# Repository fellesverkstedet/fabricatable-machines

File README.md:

# Full documention on the [wiki page](https://github.com/fellesverkstedet/fabricatable-machines/wiki)

License: [Creative commons Attribution-ShareAlike 4.0](https://creativecommons.org/licenses/by-sa/4.0/)

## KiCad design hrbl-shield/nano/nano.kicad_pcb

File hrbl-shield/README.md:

# Hrbl - Grbl shield for integrated motors

## Plug-and-play grbl controller
HRBL is an Arduiono NANO shield aiming to simplify connecting motors, limit switches, safety and spindle to an ardunio board as well as providing high quality electrical noise protection. It's tailor made for fabricatable CNC milling machine needs. 

* [PDF Schematic for JLCPCB version Nov 2019](Hrbl_shield_pdf.pdf)

## Working board with components

*Hand soldedered SMDs, card from PCBWAY*

*Hand soldered pluggable through-hole cable connectors, card from PCBWAY*
# Status
HRBL is currently in use in:
* [Hedy v1](https://github.com/fellesverkstedet/fabricatable-machines/blob/master/hedy-pcb-cnc/readme.md) A CNC milling machine made to mill circuit boards like this one.
* [At least 7 version of Humphrey](https://github.com/fellesverkstedet/fabricatable-machines/blob/master/humphrey-large-format-cnc/README.md) A large size CNC milling machine.
* [Hector](https://github.com/fellesverkstedet/fabricatable-machines/blob/master/hector-medium-format-cnc/README.md)

## Functionality
* 4 x 8 pole pluggable connections that combine all connections needed per axis in one connector per motor
* Dual connections for the y-axis, (if only one is needed this can be skipped.)
* Full optoisolation separates the computer-arduino circuit from all signal and power wires.
* Z axis milling bit probe connection with external pull-up
* Spindle control with start and speed control. Uses optocoupler for safe handling of extrernal start signal
* External power loss detection, keeps the controller in ABORT mode when there is no power to the motors.

### For use with
* Arduino Nano
* JMC ihss57 clsed loop integrated stepper motors
* 8 pole cable with 0.5mm2 wires
* 36V (10A) Power supply and cables
* Control computer or raspberry pi *(ESP8266 support coming)*
* Limit switches (optional)
* Spindle and VFD (optional)

*The shield is deigned to work with these ihss57 integrated motors and SN04-N inductive proximity sensors.*

# How to use

* [PDF Schematic for JLCPCB version Nov 2019](Hrbl_shield_pdf.pdf)

## Program the Arduino
* [Download and install arduino if you don't have it](https://www.arduino.cc/download_handler.php)
* Download the [GRBL files for arduino IDE programming with spindle enable configured](https://github.com/fellesverkstedet/fabricatable-machines/raw/master/humphrey-large-format-cnc/GRBL_Spindle_ENABLE.zip)
* Manually unzip the file in a folder. **Don't skip this step**
* Connect your arduino to your computer
* Make sure your board is set to **Arduino Nano** board in the Tool->Board menu and the serial port is selected correctly in Tool->Serial Port. (If it does not show up, try installing these [Chinese Arduino USB drivers (CH341)](https://github.com/fellesverkstedet/fabricatable-machines/blob/master/hrbl-shield/CH341SER.EXE) Then you MUST also choose Old bootloader 
)
* Now we need to add the GRBL files as a library to the Arduino program
 * In the menu go to **Sketch > Include Library** and select Add .ZIP Library. (The Add .ZIP Library command supports both a .ZIP file or a folder.) Add the folder that you unzipped.
 * You can confirm that the library has been added. Click the Sketch drop-down menu again, navigate to Include Library, then scroll to the bottom of the list where you should see grbl.
* In the menu click: File > Open, navigate to the folder Examples->Grbl, and select GrblUpload.
**Do not alter this example in any way! Grbl does not use any Arduino code. Altering this example may cause the Arduino IDE to reference Arduino code and compiling will fail.**
* Press the round arrow button to compile and **upload** Grbl to your Arduino.
* *If you can't upload try changing this in the menu: Tools > Processor > Old Bootloader*

More information about GRBL [How to use GRBL](https://github.com/gnea/grbl/wiki)

## Connect the steppers and sensors
[PDF Schematic of connections for one axis](connections_hrbl_shield_inkscape.pdf)

* The SN04-N NPN NO sensor cable colors are: Blue = GND, Brown = VCC, BLACK = SIGNAL

## Connect a spindle driver

## Connect extra alarms (OPTIONAL)
There are two pins on the signal connector that can be used to trigger an alarm. Drive them with 5V on one and GND on the other (either direction works). 

## Setup GRBL for your machine
[See the setup guide on our Wiki](https://github.com/fellesverkstedet/fabricatable-machines/wiki/GRBL-and-UGS-setup)

## Use GRBL to run your machine
[See the use guide on our wiki](https://github.com/fellesverkstedet/fabricatable-machines/wiki/How-to-use)

## Optional: HISU settings

[Required product](https://www.aliexpress.com/item/32805819281.html). 
You can also access these setting using a RS232 serial connection but the HISU device is cheap.

Recommended but not required. You can use a special handheld programming device to alter the settings in the motor drivers for the integrated stepper motors. There are two settings that are of special interest.
* P8: Open loop current This parameter affects the static torque of the motor.
* P9: Closed loop current This parameter affects the dynamic torque of the motor. (The actual current = open loop current +
close loop current)
* P16: Position error limit. If the motor detects an error bigger than this setting it will stop trying to recover the lost steps, throw an error and refuse to move until power is cycled. If I remember correctly the factory default setting allowed a full revolution before throwing an error. We recommend something much smaller to detect errors earlier. 
* P19: Speed smoothness. This is a built in acceleration setting. Since we want to control the acceleraton completely this should be set to 0.

[Full motor manual](https://github.com/fellesverkstedet/fabricatable-machines/blob/master/hrbl-shield/dev_files/integrated_stepper/20160528161106_17875.pdf)

# Ways to make the card

* The HRBL card can be ordered with SMDs assembled from [JLCPCB.com](jlcpcb.com) using these [files (previously ordered 19-11-2019)](nano/jlcpcb_order_19112019/Hrbl_grbl_19112019.zip) *Please note that the assembly preview was buggy at the time, might still be. Ignore and proceed.)*
* The plain HRBL card can be [ordered directly without components from PCBWAY using this link](https://www.pcbway.com/project/shareproject/HRBL___grbl_shield_for_Fabricatable_Machines.html)
* The HRBL card can also be [CNC milled from SVG or DXF files](hrbl-shield#files-for-milling-the-card) and the soldermask + silkscreen can be laser cut. 

## Files for milling the card

For milling the early 2019 version, works fine but is not latest version.

KiCAD files. Please note that the B-side layers are mirrored.

* [DXF](Hrbl_shield_dxf.zip)
* [KiCAD](Hrbl_shield_kicad.zip) 
* [SVG](Hrbl_shield_svg.zip)

### BOM - Electrical Components you need
* [Google sheet](https://docs.google.com/spreadsheets/d/1vCA67Y1DIPJUeFW0_8VqS5qq00QMX1T2yQB_3mDYkL8)
* [BOM PDF](Hrlb_shield_BOM_pdf.pdf)
* [BOM ODS format](Hrlb_shield_BOM_ods.ods)

### Recommended tools

* C0.4mm 2 flute china endmill, 8 mm/s @18000rpm
* 1 mm flat endmill, for holes and cutout 
* FR1, FR2 or FR3 double sided PCB stock. (NOT FR4, since it has fiberglass in it and wears out your bit fast)
* Ø6mm dowels/pegs for indexing the card when flipping it. Milling bit with Ø6mm shaft can be used.

#### Using Vcarve and a CNC mill

* Download the DXF files
* Unzip the files
* Mill the bed flat or put in a small piece of scrap wood and mill that flat
* Secure the card with double stick tape
* **Side: BACK Load file: B.Cu Use bit: Ø0.4mm** First, **MIRROR THE FILE VERTICALLY** Then use a pocket operation to create insulation between the copper traces. Pocket to 0.1-0.3 mm deep.
* **Side: BACK: Use bit: Ø1**  Mill the (vias) circular holes to Ø1.1 to Ø1.2 mm, no more no less. 
* **Side: BACK: Bit: Ø1mm** Draw two Ø6mm index holes on the stock outside the vectors, they form the mirror line. Pocket mill them down into the material below the card, 4 mm below should be enough. 
* **Side: BACK: Item: Dowel peg** Test the holes with the dowel, they should not be too tight or you might crack the card. Too lose = bad precision.
* **FLIP CARD** Take the card off the tape, add new tape and use the dowels to position the card.
* **Side FRONT: load file: F.Cu Use bit: Ø0.4mm** First, compare the position of the small holes to your CAM view and see that you have the correct orientation of the file. Then pocket the copper to 0.1-0.3 mm deep.
* **Side: FRONT Use bit: Ø1mm** Cut the big mounting holes, then cut out the card, a larger bit can be used if you want too. 

#### Lasercut the soldemask and silkscreen

*Front of card - Silkscreen layer*

*Back of card - Silkscreen and solder mask layers, here shown mirrored compared to the files*

Both sides are covered with a [special laser-engraving sicker film](img/laser_sheets_specs.JPG) purchased from [Alvøen](alvoen.no) which protects the card, functions as a solder mask and silkscreen print.

* Use a lasercutter and move the focus height to the top of th film!

## Soldering the SMDs
Remember to put the 3 diodes, 1 LED and 15 optocoplers in the correct orientation. Also check print on board for orientation of the green connectors.

### Production photos

## Notes from previous milling 

* Careful with which layer you mirror when you mill it!
* 8mm/s @18000rpm with a Ø0.4mm 2 flute china endmill worked! (did most with 4.5mm/s)
* Attach with double sided skotch tape (Jernia-brand worked well)
* Mill and drill from the side where you will solder the most thorugh hole components first
* Drilled Ø1mm holes were too tight for the contacts, mill them to at least Ø1,2mm next time.
* Don't make the alignment holes for flipping the card too tight.

## Board house PCB

Plain board manufactured by PCB Way from KiCAD gerber files.

* [Gerber files](gerber/nano-hrbl.zip)
* [Order directily on PCB Way](https://www.pcbway.com/project/shareproject/HRBL___grbl_shield_for_Fabricatable_Machines.html)

### Future ideas and things to do
* HRBL-shield is potentially great to combine with [Hertz - axis monitoring board](https://github.com/fellesverkstedet/fabricatable-machines/tree/master/hertz-axis-monitor). Optimized for ihss57 integrated closed loop stepper motors.
* Create a version with a onboard 328p microprocessor to be able to skip the arduino uno altogether, remember to breakout programming pins for the MCU
* Consider replacing the 16 single channel SFH6206-3T optocouplers with 4 channel 4TLP291-4(GB) for reduced part count and cheaper BOM. 
* (From [issue 20](https://github.com/fellesverkstedet/fabricatable-machines/issues/20) consider if we should change the 5V voltage regulator.
* Establish a maximum current that we can draw through the card to the motors without overheating the traces (or ribbon cable).
* Add dual axis squaring
* Change the ZIP filename so that you don't need to unzip GRBL
* Consider 3 pin plugs for sensors

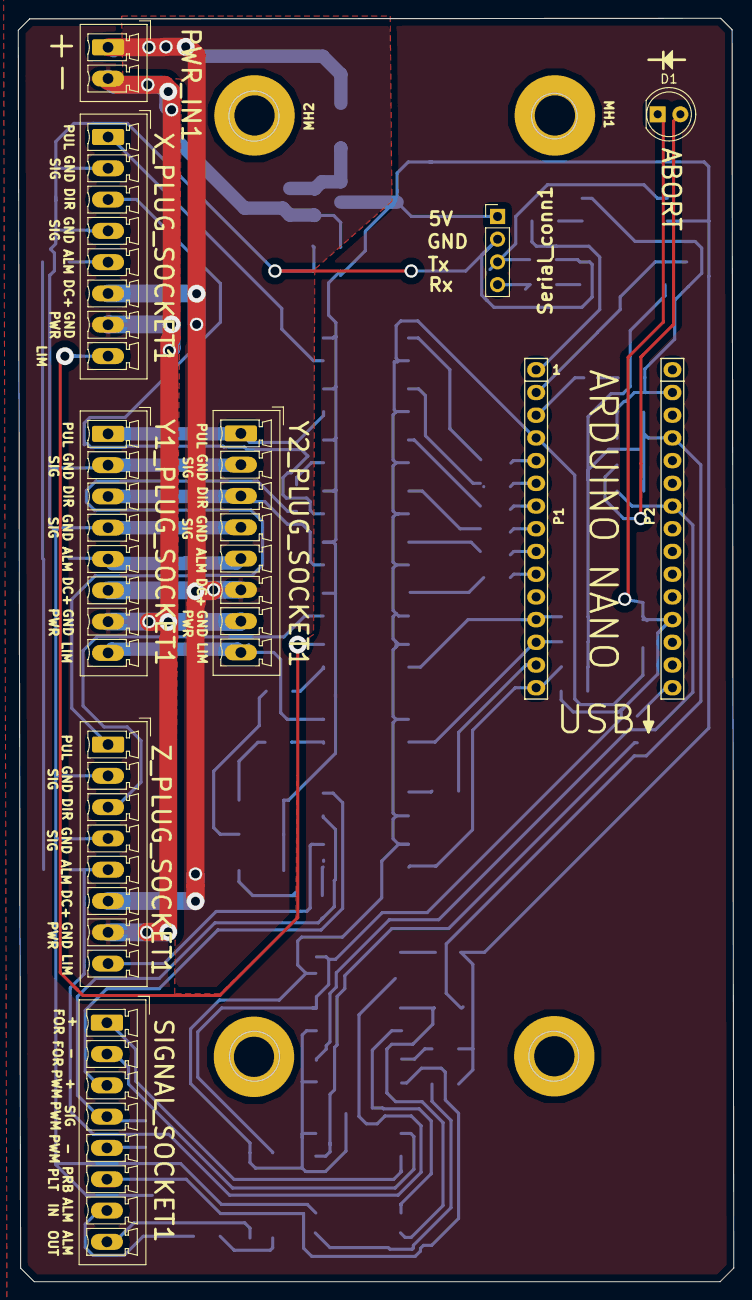
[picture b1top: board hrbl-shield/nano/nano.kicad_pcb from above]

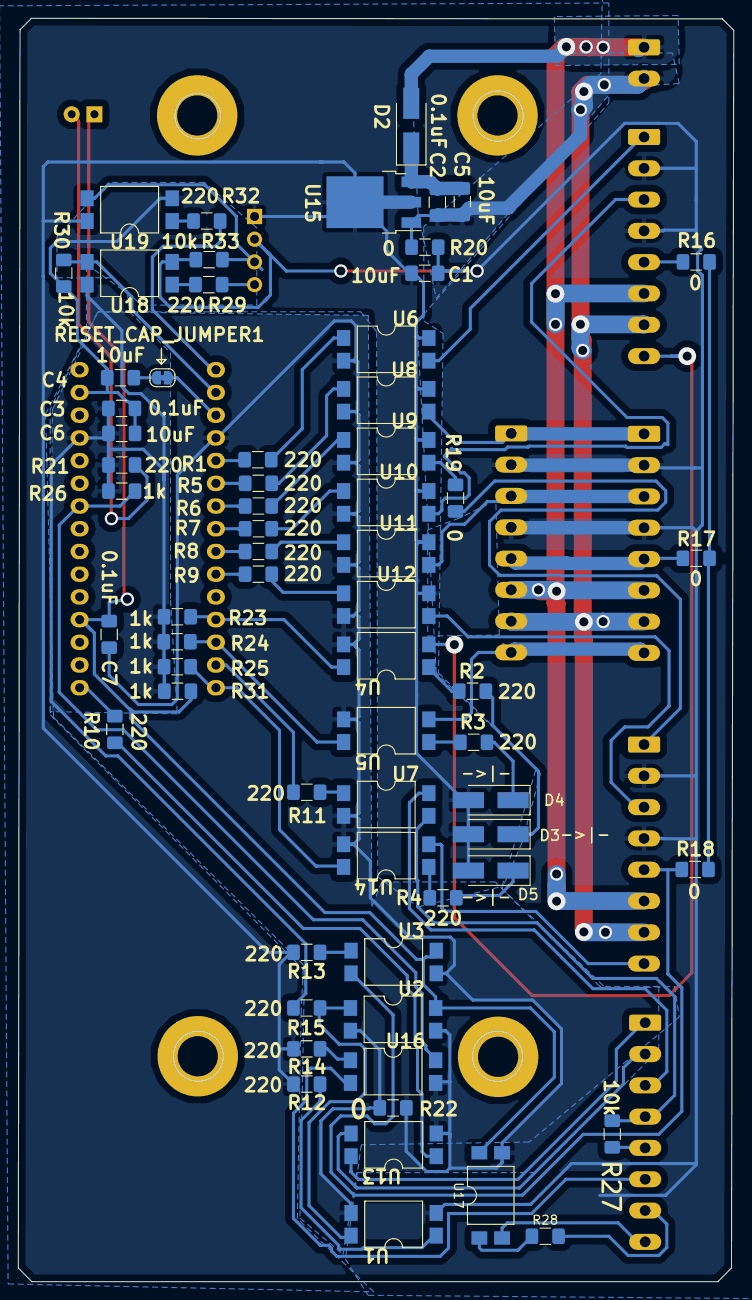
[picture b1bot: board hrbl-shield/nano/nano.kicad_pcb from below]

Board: 2 copper layers, 80.0 x 141.3 mm, 78 parts (64 on the bottom side), 67 nets.

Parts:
C1, C4, C5, C6: 10uF; C_1206_3216Metric_Pad1.42x1.75mm_HandSolder
C2, C3, C7: 0.1uF; C_1206_3216Metric_Pad1.42x1.75mm_HandSolder
D1: LED (20mA 1.85V); LED_D5.0mm
D2, D3, D4, D5: 1N4007; D_SMA_Handsoldering
MH1, MH2, MH3, MH4: MountingHole; MountingHole_4.5mm_Pad
P1: Digital; Socket_Strip_Arduino_1x15
P2: Analog; Socket_Strip_Arduino_1x15
PWR_IN1: Conn_01x02; PhoenixContact_MCV_1,5_2-G-3.5_1x02_P3.50mm_Vertical
R1, R2, R3, R4, R5, R6, R7, R8, R9, R10, R11, R12, R13, R14, R15, R21, R28, R29, R32: 220; R_1206_3216Metric_Pad1.42x1.75mm_HandSolder
R16, R17, R18, R19, R20, R22: 0; R_1206_3216Metric_Pad1.42x1.75mm_HandSolder
R23, R24, R25, R26, R31: 1k; R_1206_3216Metric_Pad1.42x1.75mm_HandSolder
R27, R30, R33: 10k; R_1206_3216Metric_Pad1.42x1.75mm_HandSolder
RESET_CAP_JUMPER1: SolderJumper-2_P1.3mm_Bridged_RoundedPad1.0x1.5mm
SIGNAL_SOCKET1: Conn_01x08; PhoenixContact_MCV_1,5_8-G-3.5_1x08_P3.50mm_Vertical
Serial_conn1: Conn_01x04; PinHeader_1x04_P2.54mm_Vertical
U1, U2, U3, U4, U5, U6, U7, U8, U9, U10, U11, U12, U13, U14, U16, U17, U18, U19: SFH6206-3T; SMDIP-4_W9.53mm_Clearance8mm
U15: IFX27001TFV50ATMA1CT-ND; TO-252-3_TabPin2
X_PLUG_SOCKET1: Conn_01x08; PhoenixContact_MCV_1,5_8-G-3.5_1x08_P3.50mm_Vertical
Y1_PLUG_SOCKET1, Y2_PLUG_SOCKET1: Conn_01x08; PhoenixContact_MCV_1,5_8-G-3.5_1x08_P3.50mm_Vertical
Z_PLUG_SOCKET1: Conn_01x08; PhoenixContact_MCV_1,5_8-G-3.5_1x08_P3.50mm_Vertical

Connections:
5V_ISO: C1.1, D3.2, D4.2, D5.2, R12.2, R13.2, R14.2, Serial_conn1.1, U6.4, U8.4, U9.4, U10.4, U11.4, U12.4, U15.2, U19.4
+5V: C3.2, C6.2, P2.4, R15.2, R21.2, R23.1, R24.1, R25.1, R26.1, R31.2, U18.4
+36V: D2.2, PWR_IN1.1, X_PLUG_SOCKET1.6, Y1_PLUG_SOCKET1.6, Y2_PLUG_SOCKET1.6, Z_PLUG_SOCKET1.6
ABORT: C7.2, D1.1, P2.12, R31.1, U2.4, U3.4, U17.4
ALARM_IN: R16.1, R16.2, R17.1, R17.2, R18.1, R18.2, U3.2, X_PLUG_SOCKET1.5, Y1_PLUG_SOCKET1.5, Y2_PLUG_SOCKET1.5, Z_PLUG_SOCKET1.5
DIR_X: P1.8, R7.2
DIR_X_OUT: U10.3, X_PLUG_SOCKET1.3
DIR_Y: P1.9, R8.2
DIR_Y_OUT: U11.3, Y1_PLUG_SOCKET1.3, Y2_PLUG_SOCKET1.3
DIR_Z: P1.10, R9.2
DIR_Z_OUT: U12.3, Z_PLUG_SOCKET1.3
EXTRA_ALARM_IN: R28.2, SIGNAL_SOCKET1.7
EXTRA_ALARM_OUT: SIGNAL_SOCKET1.8, U17.2
GND: C3.1, C4.1, C6.1, C7.1, P1.4, P2.2, R22.1, R22.2, R30.1, U1.3, U2.2, U2.3, U3.3, U4.3, U5.3, U6.2, U7.2, U8.2, U9.2, U10.2, U11.2, U12.2, U13.2, U14.3, U16.3, U17.3, U19.2
GNDPWR: C2.2, C5.2, PWR_IN1.2, R20.2, U15.1, X_PLUG_SOCKET1.7, Y1_PLUG_SOCKET1.7, Y2_PLUG_SOCKET1.7, Z_PLUG_SOCKET1.7
GNDS: C1.2, R20.1, R33.1, Serial_conn1.2, U1.2, U18.2, X_PLUG_SOCKET1.2, X_PLUG_SOCKET1.4, Y1_PLUG_SOCKET1.2, Y1_PLUG_SOCKET1.4, Y2_PLUG_SOCKET1.2, Y2_PLUG_SOCKET1.4, Z_PLUG_SOCKET1.2, Z_PLUG_SOCKET1.4
GND_FOR: SIGNAL_SOCKET1.2, U13.3
GND_SPEED: R27.1, SIGNAL_SOCKET1.5
LIM_X: P1.12, R23.2, U4.4
LIM_X_IN: U4.2, X_PLUG_SOCKET1.8
LIM_Y: P1.13, R24.2, U5.4
LIM_Y_IN: U5.2, Y1_PLUG_SOCKET1.8, Y2_PLUG_SOCKET1.8
LIM_Z: P1.15, R25.2, U14.4
LIM_Z_IN: U14.2, Z_PLUG_SOCKET1.8
unnamed: C2.1, C5.1, D2.1, U15.3
unnamed: C4.2, RESET_CAP_JUMPER1.2
unnamed: D1.2, R21.1
unnamed: D3.1, R2.2
unnamed: D4.1, R3.2
unnamed: D5.1, R4.2
unnamed: R1.1, U6.1
unnamed: R2.1, U4.1
unnamed: R3.1, U5.1
unnamed: R4.1, U14.1
unnamed: R5.1, U8.1
unnamed: R6.1, U9.1
unnamed: R7.1, U10.1
unnamed: R8.1, U11.1
unnamed: R9.1, U12.1
unnamed: R10.1, U13.1
unnamed: R11.1, U7.1
unnamed: R12.1, U1.1
unnamed: R13.1, U3.1
unnamed: R14.1, U16.1
unnamed: R15.1, U1.4, U2.1
unnamed: R19.2, U9.3
unnamed: R28.1, U17.1
unnamed: R29.1, U18.1
unnamed: R32.1, U19.1
PROBE: P2.7, R26.2, U16.4
PROBE_PLATE: SIGNAL_SOCKET1.6, U16.2
PUL_X: P1.5, R1.2
PUL_X_OUT: U6.3, X_PLUG_SOCKET1.1
PUL_Y: P1.6, R5.2
PUL_Y_OUT: U8.3, Y1_PLUG_SOCKET1.1, Y2_PLUG_SOCKET1.1
PUL_Z: P1.7, R6.2
PUL_Z_OUT: R19.1, Z_PLUG_SOCKET1.1
RESET: P1.3, RESET_CAP_JUMPER1.1
Rx: P1.2, R30.2, U18.3
Rx_conn: R29.2, Serial_conn1.4
SIGNAL_SPEED: R27.2, SIGNAL_SOCKET1.4, U7.3
SOURCE_FOR: SIGNAL_SOCKET1.1, U13.4
SOURCE_SPEED: SIGNAL_SOCKET1.3, U7.4
SPINDLE_EN: P2.15, R10.2
SPINDLE_PWM: P1.14, R11.2
Tx: P1.1, R32.2
Tx_conn: R33.2, Serial_conn1.3, U19.3

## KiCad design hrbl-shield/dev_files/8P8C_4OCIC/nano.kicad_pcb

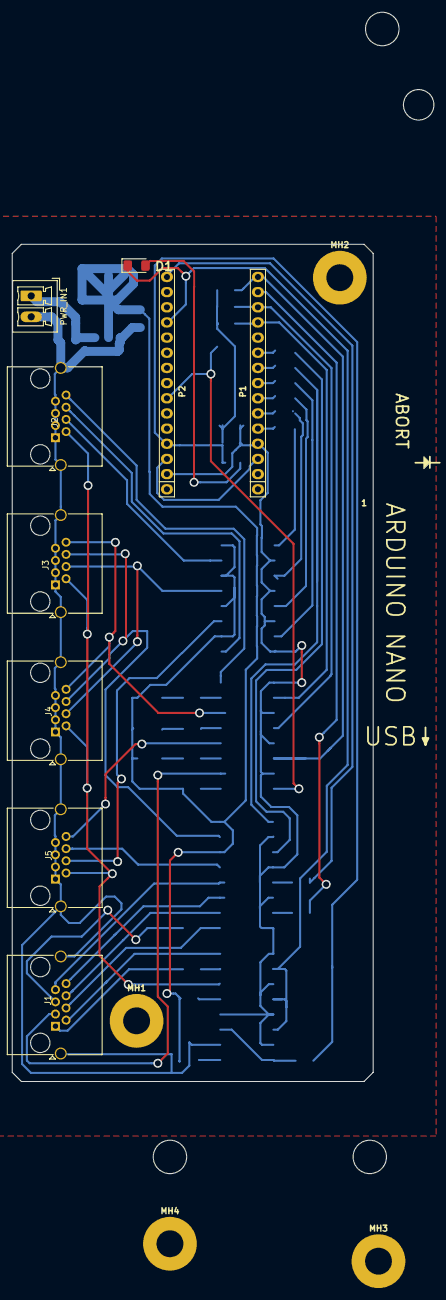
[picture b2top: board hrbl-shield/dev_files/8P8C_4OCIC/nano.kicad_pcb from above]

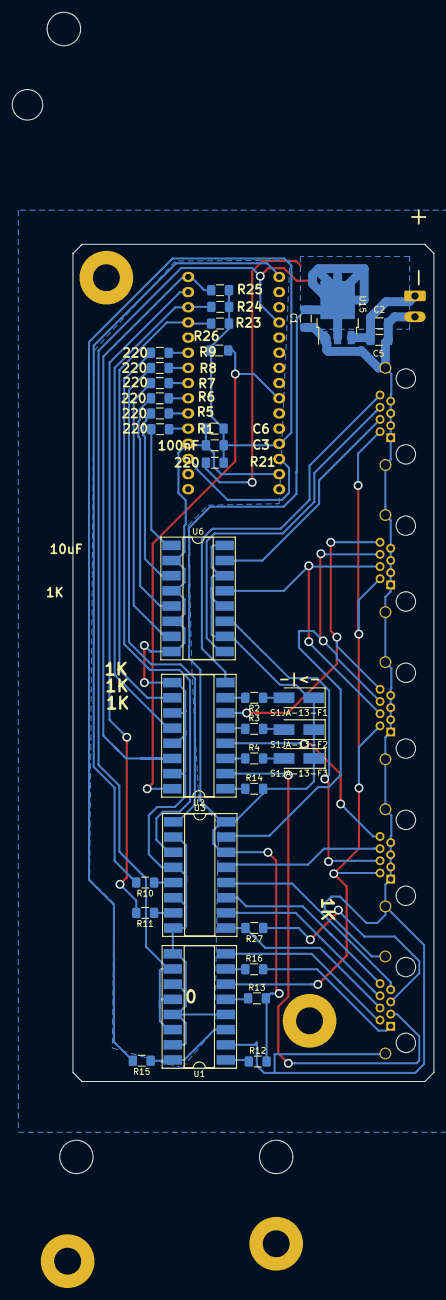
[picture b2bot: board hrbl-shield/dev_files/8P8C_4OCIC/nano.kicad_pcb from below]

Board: 2 copper layers, 60.5 x 140.2 mm, 48 parts (35 on the bottom side), 57 nets.

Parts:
C1, C5, C6: 10uF; C_1206_3216Metric_Pad1.42x1.75mm_HandSolder
C2: 100nF (0.1uF); C_1206_3216Metric_Pad1.42x1.75mm_HandSolder
C3: 100nF; C_1206_3216Metric_Pad1.42x1.75mm_HandSolder
D1: LED; LED_1206_3216Metric_Pad1.42x1.75mm_HandSolder
J1: 8P8C_Shielded SIG; RJ45_Amphenol_RJHSE5380
J2: 8P8C_Shielded X; RJ45_Amphenol_RJHSE5380
J3: 8P8C_Shielded Y; RJ45_Amphenol_RJHSE5380
J4: 8P8C_Shielded Y2; RJ45_Amphenol_RJHSE5380
J5: 8P8C_Shielded Z; RJ45_Amphenol_RJHSE5380
MH1, MH2, MH3, MH4: MountingHole; MountingHole_4.5mm_Pad
P1: Digital; Socket_Strip_Arduino_1x15
P2: Analog; Socket_Strip_Arduino_1x15
PWR_IN1: Conn_01x02; PhoenixContact_MCV_1,5_2-G-3.5_1x02_P3.50mm_Vertical
R1, R2, R3, R4, R5, R6, R7, R8, R9, R10, R11, R12, R13, R14, R15, R16, R21: 220; R_1206_3216Metric_Pad1.42x1.75mm_HandSolder
R23, R24, R25, R26, R27: 1000; R_1206_3216Metric_Pad1.42x1.75mm_HandSolder
S1JA-13-F1, S1JA-13-F2, S1JA-13-F3: DIODE; D_SMA_Handsoldering
U1, U2, U3, U6: LTV-844; DIP-16_W8.89mm_SMDSocket_LongPads
U15: IFX27001TFV50ATMA1CT-ND; TO-252-3_TabPin2

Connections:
5V_ISO: C1.1, R12.2, R13.2, R14.2, S1JA-13-F1.1, S1JA-13-F2.1, S1JA-13-F3.1, U3.14, U3.16, U6.10, U6.12, U6.14, U6.16, U15.2
+5V: C3.2, C6.2, P2.4, R15.2, R21.2, R23.1, R24.1, R25.1, R26.1
+36V: C2.1, C5.1, PWR_IN1.1, U15.3
/Invert: R15.1, U1.3, U1.16
/Reset: P1.3, P2.3
ABORT: D1.1, P2.12, U1.10, U1.12, U1.14
ALARM_EXTRA_1: J1.1, R16.2
ALARM_EXTRA_2: J1.2, U1.8
ALARM_IN: J2.2, J3.2, J4.2, J5.2, U1.6
DIR_X: P1.8, R7.2
DIR_X_OUT: J2.6, U6.9
DIR_Y: P1.9, R8.2
DIR_Y_OUT: J3.6, J4.6, U3.15
DIR_Z: P1.10, R9.2
DIR_Z_OUT: J5.6, U3.13
GND: C3.1, C6.1, P1.4, P2.2, U1.4, U1.9, U1.11, U1.13, U1.15, U2.9, U2.11, U2.13, U2.15, U3.2, U3.4, U3.6, U3.8, U6.2, U6.4, U6.6, U6.8
GNDS: C1.2, C2.2, C5.2, J1.SH, J2.1, J2.3, J2.5, J2.7, J2.SH, J3.1, J3.3, J3.5, J3.7, J3.SH, J4.1, J4.3, J4.5, J4.7, J4.SH, J5.1, J5.3, J5.5, J5.7, J5.SH, PWR_IN1.2, U1.2, U15.1
GND_FOR: J1.8, U3.11
GND_SPEED: J1.5, R27.1
LIM_X: P1.12, R23.2, U2.10
LIM_X_IN: J2.8, U2.8
LIM_Y: P1.13, R24.2, U2.12
LIM_Y_IN: J3.8, J4.8, U2.6
LIM_Z: P1.15, R25.2, U2.14
LIM_Z_IN: J5.8, U2.4
unnamed: D1.2, R21.1
unnamed: R1.1, U6.1
unnamed: R2.1, U2.7
unnamed: R2.2, S1JA-13-F1.2
unnamed: R3.1, U2.5
unnamed: R3.2, S1JA-13-F2.2
unnamed: R4.1, U2.3
unnamed: R4.2, S1JA-13-F3.2
unnamed: R5.1, U6.3
unnamed: R6.1, U6.5
unnamed: R7.1, U6.7
unnamed: R8.1, U3.1
unnamed: R9.1, U3.3
unnamed: R10.1, U3.5
unnamed: R11.1, U3.7
unnamed: R12.1, U1.1
unnamed: R13.1, U1.5
unnamed: R14.1, U2.1
unnamed: R16.1, U1.7
PROBE: P2.7, R26.2, U2.16
PROBE_PLATE: J1.3, U2.2
PUL_X: P1.5, R1.2
PUL_X_OUT: J2.4, U6.15
PUL_Y: P1.6, R5.2
PUL_Y_OUT: J3.4, J4.4, U6.13
PUL_Z: P1.7, R6.2
PUL_Z_OUT: J5.4, U6.11
SIGNAL_SPEED: J1.4, R27.2, U3.9
SOURCE_FOR: J1.7, U3.12
SOURCE_SPEED: J1.6, U3.10
SPINDLE_EN: P2.15, R10.2
SPINDLE_PWM: P1.14, R11.2

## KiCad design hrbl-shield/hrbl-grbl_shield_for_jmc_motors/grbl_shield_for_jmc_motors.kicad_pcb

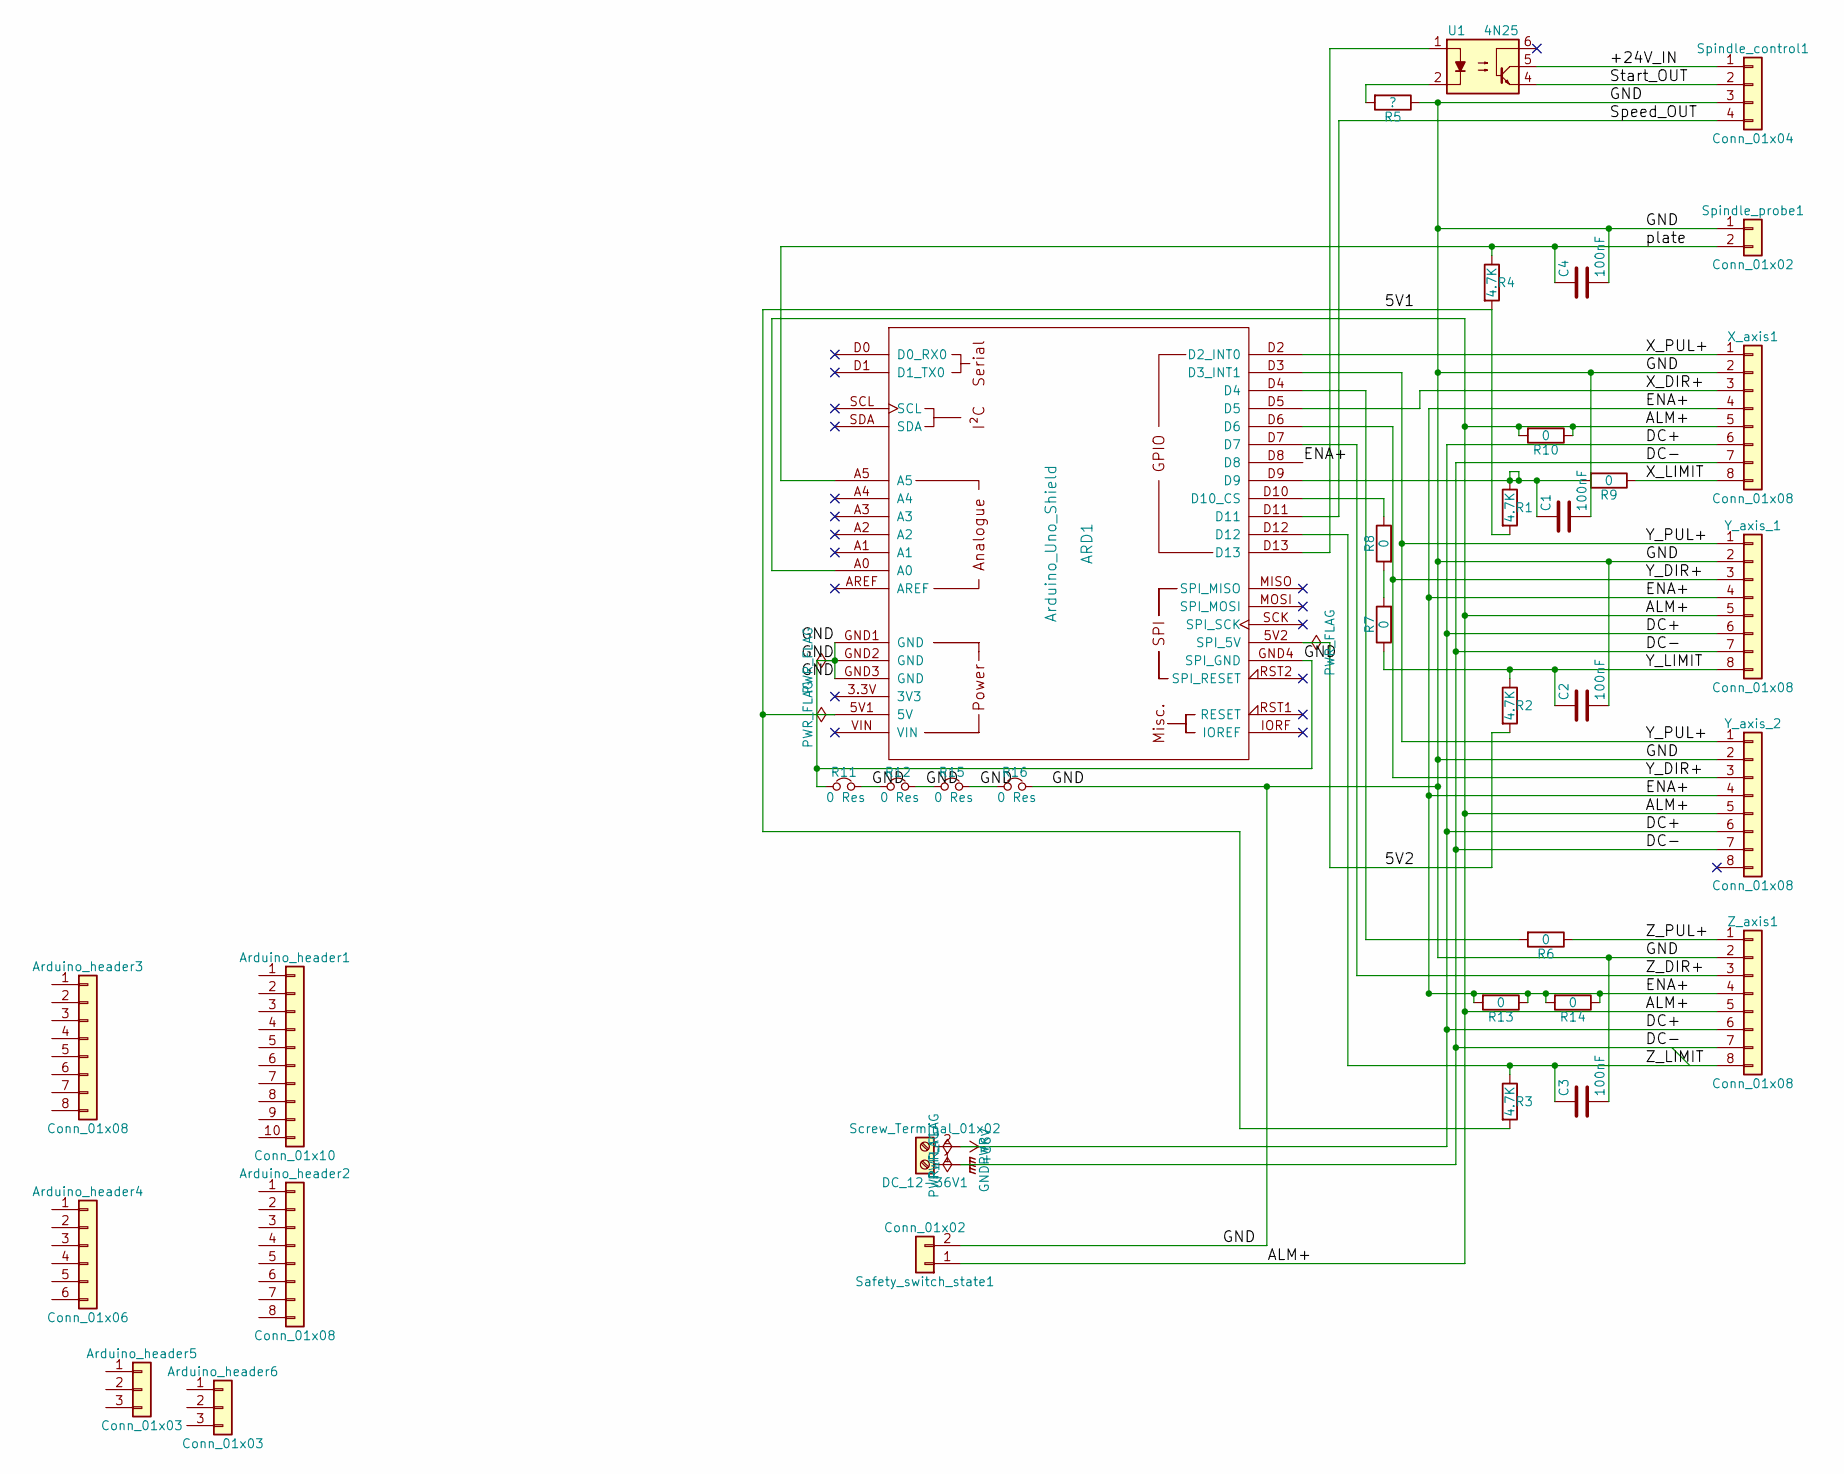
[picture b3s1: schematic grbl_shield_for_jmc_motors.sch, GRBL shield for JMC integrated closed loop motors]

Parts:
ARD1: Arduino_Uno_Shield
Arduino_header1: Conn_01x10; Pin_Header_Straight_1x10_Pitch2.54mm
Arduino_header2, Arduino_header3: Conn_01x08; Pin_Header_Straight_1x08_Pitch2.54mm
Arduino_header4: Conn_01x06; Pin_Header_Straight_1x06_Pitch2.54mm
Arduino_header5, Arduino_header6: Conn_01x03; Socket_Strip_Straight_1x03_Pitch2.54mm
C1, C2, C3, C4: 100nF; C_1206_HandSoldering
DC_12-36V1: Screw_Terminal_01x02; TerminalBlock_Phoenix_MPT-2.54mm_2pol
R1, R2, R3, R4: 4.7K; R_1206_HandSoldering
R5: ?; R_1206_HandSoldering
R6, R7, R8, R9, R10, R13, R14: 0; R_1206_HandSoldering
R11, R12, R15, R16: 0 Res; R_1206_HandSoldering
Safety_switch_state1: Conn_01x02; Pin_Header_Straight_1x02_Pitch2.54mm
Spindle_control1: Conn_01x04; Pin_Header_Straight_1x04_Pitch2.54mm
Spindle_probe1: Conn_01x02; Pin_Header_Straight_1x02_Pitch2.54mm
U1: 4N25; DIP-6_W7.62mm
X_axis1: Conn_01x08; Pin_Header_Straight_1x08_Pitch2.54mm
Y_axis_1, Y_axis_2: Conn_01x08; Pin_Header_Straight_1x08_Pitch2.54mm
Z_axis1: Conn_01x08; Pin_Header_Straight_1x08_Pitch2.54mm

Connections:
+36V: DC_12-36V1.2, X_axis1.6, Y_axis_1.6, Y_axis_2.6, Z_axis1.6
/5V1: ARD1.5V1 (5V), R1.2, R3.2, R4.2
/5V2: ARD1.5V2 (SPI_5V), R2.2
/+24V_IN: Spindle_control1.1, U1.5
/ALM+: ARD1.A0, R10.1, R10.2, Safety_switch_state1.1, X_axis1.5, Y_axis_1.5, Y_axis_2.5, Z_axis1.5
/ENA+: ARD1.D8, R13.1, R13.2, R14.1, R14.2, X_axis1.4, Y_axis_1.4, Y_axis_2.4, Z_axis1.4
/GND: ARD1.GND1 (GND), ARD1.GND2 (GND), ARD1.GND3 (GND), ARD1.GND4 (SPI_GND), C1.2, C2.2, C3.2, C4.2, R5.1, R11.1, R11.2, R12.1, R12.2, R15.1, R15.2, R16.1, R16.2, Safety_switch_state1.2, Spindle_control1.3, Spindle_probe1.1, X_axis1.2, Y_axis_1.2, Y_axis_2.2, Z_axis1.2
/Speed_OUT: ARD1.D11, Spindle_control1.4
/Start_OUT: Spindle_control1.2, U1.4
/X_DIR+: ARD1.D5, X_axis1.3
/X_LIMIT: R9.1, X_axis1.8
/X_PUL+: ARD1.D2 (D2_INT0), X_axis1.1
/Y_DIR+: ARD1.D6, Y_axis_1.3, Y_axis_2.3
/Y_LIMIT: C2.1, R2.1, R7.1, Y_axis_1.8
/Y_PUL+: ARD1.D3 (D3_INT1), Y_axis_1.1, Y_axis_2.1
/Z_DIR+: ARD1.D7, Z_axis1.3
/Z_LIMIT: ARD1.D12, C3.1, R3.1, Z_axis1.8
/Z_PUL+: R6.1, Z_axis1.1
/plate: ARD1.A5, C4.1, R4.1, Spindle_probe1.2
GNDPWR: DC_12-36V1.1, X_axis1.7, Y_axis_1.7, Y_axis_2.7, Z_axis1.7
unnamed: ARD1.D4, R6.2
unnamed: ARD1.D9, C1.1, R1.1, R9.2
unnamed: ARD1.D10 (D10_CS), R8.1
unnamed: ARD1.D13, U1.1
unnamed: R5.2, U1.2
unnamed: R7.2, R8.2

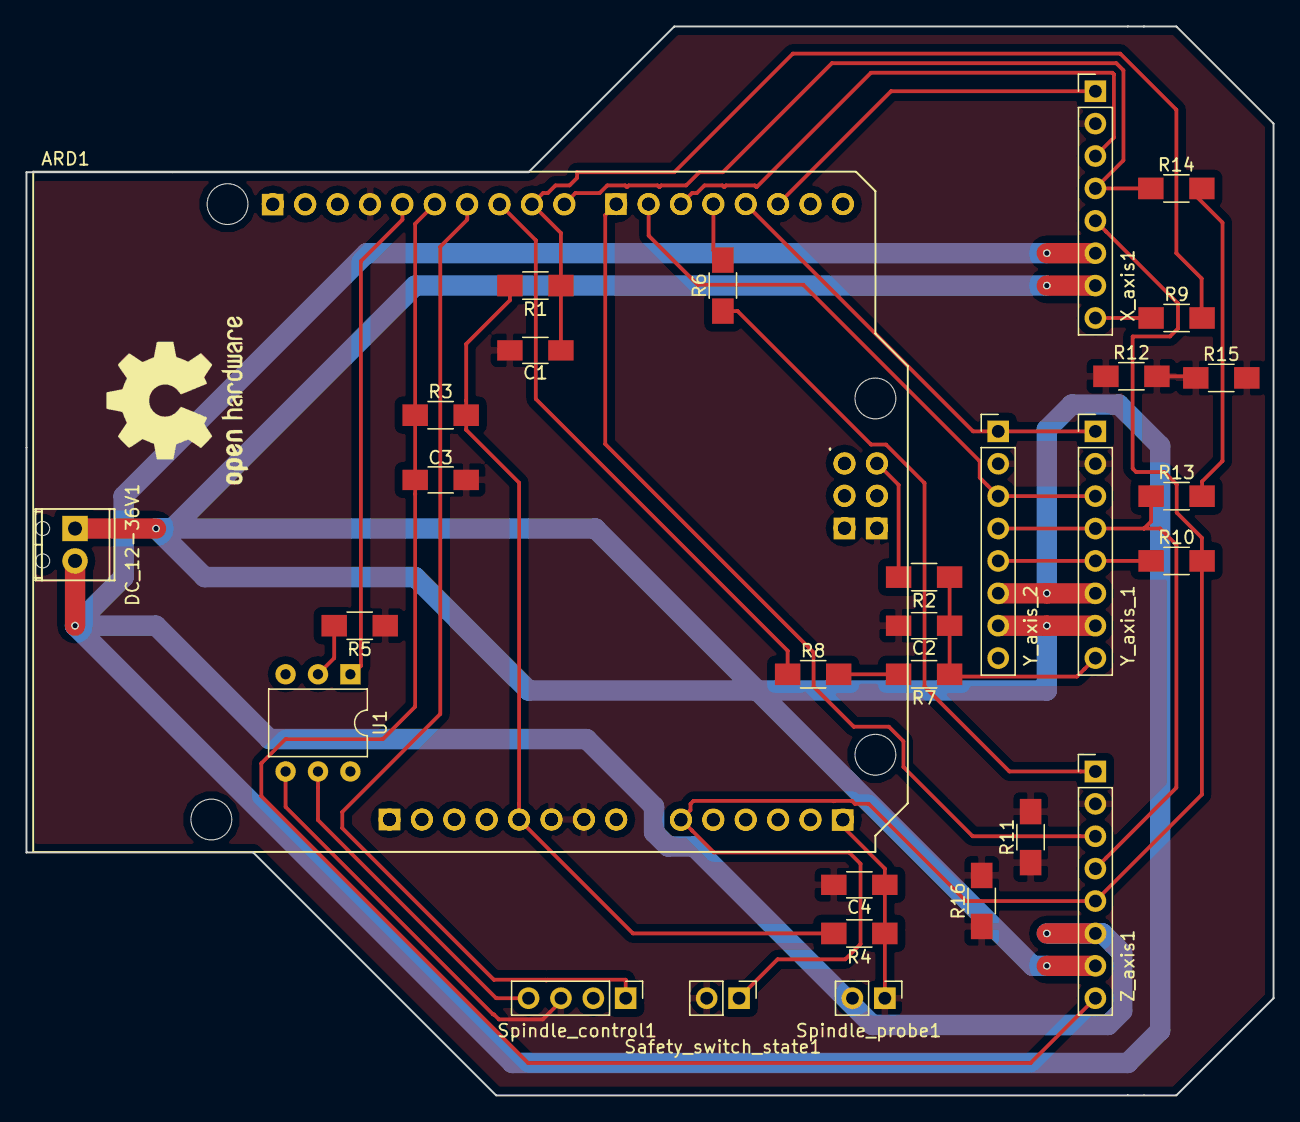
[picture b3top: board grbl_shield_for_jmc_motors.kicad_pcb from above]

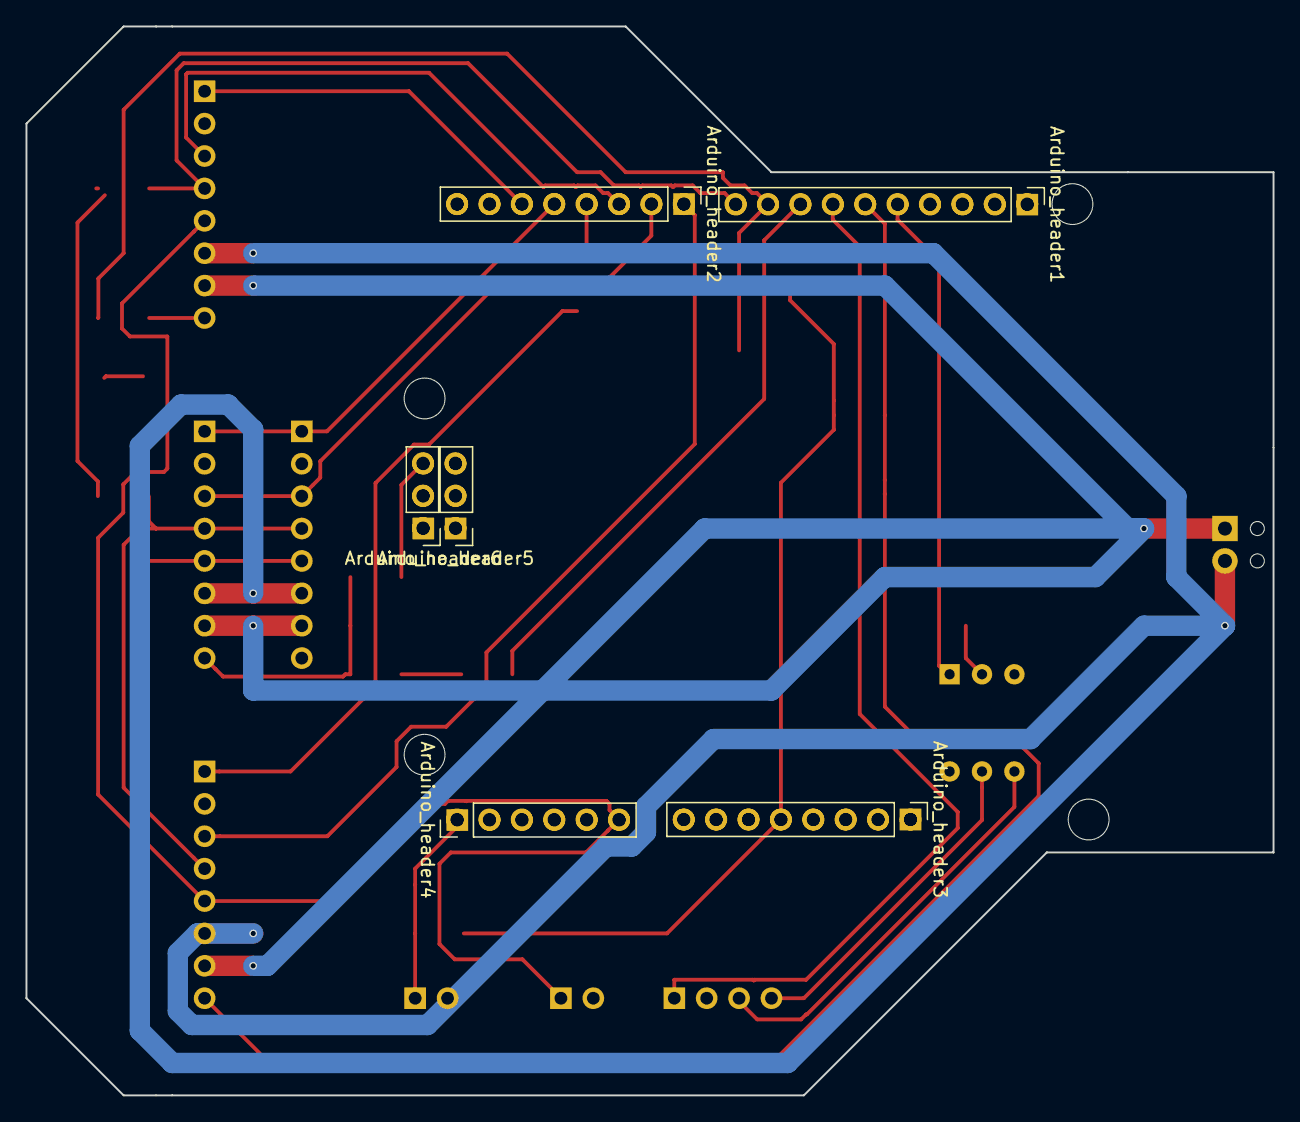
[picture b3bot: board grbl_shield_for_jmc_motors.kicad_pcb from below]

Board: 2 copper layers, 97.8 x 83.8 mm, 36 parts (6 on the bottom side), 26 nets.

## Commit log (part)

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2018-12-12 tilt spidle
2018-12-12 motor pics
2018-12-12 Y wheel sideways
2018-12-12 axis
2018-12-12 Z/rollers
2018-12-12 Spindle_pics
2018-12-13 Lower dust and top dust
2018-12-13 Dust pics
2019-01-23 Nano notes
2019-01-23 Pics!
2019-01-29 pics for alu milling
2019-01-29 Smaller pics
2019-01-29 Flipped pics
2019-01-29 resize pics
2019-01-29 added pics
2019-01-29 More pics
2019-01-29 More instructions
2019-01-29 Costs
2019-01-29 Removed unfinished files
2019-01-29 graphs
2019-01-29 Spare graph
2019-01-29 BOM in other formats
2019-01-30 Reorganised humphrey folder structure
    Not fixed all links yet
2019-01-31 Vfd wireing guide
2019-02-19 Upgraded ALU cut sheets
2019-02-19 Fixed links
2019-02-19 Fixed links and titles
2019-02-19 Fixed link
2019-02-19 Fixed broken image links
2019-02-19 Link repair
2019-02-20 fixed links and changed descriptions
2019-02-20 All 4 humphery and link fix
2019-02-20 Added links for easier navigation
2019-02-20 added milling gif
2019-03-04 Updated dxf files for table
2019-03-15 Alu spindle mount
2019-03-18 hrbl shield updated and folder cleaned
2019-03-18 added backside hrlb shield
2019-03-18 started work on wood sheet based humphrey
    meant to be very fast to fabricate and easy to hack, yet have decent performance
2019-03-25 Create humphrey5-at-kuben-cropped.jpg
    added image of humphrey number 5 at kuben high school
2019-03-25 updated front page photo of humphrey
2019-03-25 added work in progress files for wood humphrey
2019-03-29 started documentation on wood version
2019-03-29 added render and cut sheets for humphrey wood version
2019-03-29 updated docu and bom
2019-03-29 fixed typos and added power supply
2019-03-29 added wood version link and tweaked layout
2019-03-29 tweaked layout
2019-03-29 tweaked BOM
2019-03-29 fixed typo
2019-04-03 updated with alternative spindle
2019-04-07 updated humphrey wood version files
    also added 3d printable version of pinion
2019-04-07 Updated links to parts and bill of materials
2019-04-27 fixed broken links to cutsheet
2019-04-28 Kicad edits
2019-04-28 Updated total alu cutsheet to match latest part edits and cleaned paths
2019-05-01 humphrey wood version f360 file
    An update with the humphrey wood version fusion 360 file where the parts have been named, put into groups, and ordered in a suggested order of assembly. Also updated wood_version_how_to_make
2019-05-26 Added Bark beetle CAM for Humphrito
    Dependables: Rhino6 on windows
2019-05-26 Update feeds and speeds for alu milling
2019-06-07 Added Vcarve and gcode
    Added Vcarve and gcode files for wooden Humphrey
2019-06-07 added note about vcarve and gcode files
2019-06-15 Added geometry for standardized testing of machines
2019-06-17 added new test geometry for cutting all the way through
2019-06-17 depricated
2019-06-29 Gerber files and new generation tests
2019-06-29 saved
2019-07-01 Simulation of AC detection criquit
    https://www.falstad.com/circuit/
    3,6 k for 220V and 600 ohm for 36V. The other components stay the same.
    use a AC optocoupler to save a component. The ones we have used previously are SFH6206-3T
2019-07-01 Kicad of ac detector
2019-07-01 HRBL with ethernet and spindle stall detection
2019-07-01 Moved arduino to corner and added spindle alarm
2019-07-01 Added spindle fault Abort to old card
2019-07-26 Added professional PCB
2019-08-20 HRBL soldered board
    pictures of HRBL with components and note.
2019-08-29 Different spindle control generations
2019-08-29 wireless stepper module in development
2019-08-29 readme added to wireless motor
2019-09-03 Added test results Wifi stepper
2019-09-09 Strip board prototype plans
2019-09-10 Safety circiuts research
2019-09-17 roadmap to highway
2019-09-21 Documenting wiring
2019-09-21 spinde-set manual and images
2019-09-21 missing cable and connector
2019-09-23 hobo, not humphrey
2019-09-25 milling mkI spindle files
2019-10-08 Reconstructed hattori autohoming post processor
    Not tested as of 08.10.2019.
2019-10-08 Corrected too high finishing Y position
2019-10-15 grbl upload update
2019-10-15 Old bootloader
2019-10-15 Italics
2019-10-15 Java UGS fix
2019-10-15 ugs platform
2019-10-15 Improved instructions
2019-10-15 Java to UGS
2019-11-07 Inverter manual pdf upload
2019-11-16 Added serial pins and more noise protection
2019-11-16 JLCPCB test files and added logo
2019-11-16 Lots of JLCPCB tests
2019-11-17 more jlcpcb testing
2019-11-19 jlcpcb ordered
2019-11-21 Schematic pics
2019-11-21 Media files of wooden Humphrey
    Added link to google drive with pictures and video of wooden Humphrey build by Haakon Walseng.
2019-11-22 Images of bootstrap mill 3D+laser
2019-11-24 Rename readme
2019-11-24 Updated roller pics
2019-11-25 Spindle illustrations
2019-12-07 Spindle
    Spindle update update
2019-12-09 spindle setup txt to md
    spindle setup txt to md
2019-12-09 file rename
    file rename
2019-12-09 Spindle pictures and readme
    Spindle pictures and readme
2019-12-09 Spindle cleanup
    Spindle cleanup
2019-12-10 Spindle readme update
    Spindle readme update
2019-12-16 Added meetup folder
    Added meetup folder with description and link to media files.
2019-12-16 meetup update
    meetup update
2019-12-16 meetup update
    meetup update. broken link
2019-12-16 meetup readme format
    meetup readme format
2019-12-16 meetup corrections
    yet another meetup correction. v5 description
2019-12-16 hard endstops stl wooden humphrey
    hard endstops stl for wooden humphrey.
    WIP, but something to work from. See readme for advice.
2019-12-16 endstop update to readme, wooden humphrey
    endstop update to readme, wooden humphrey
2019-12-16 hard endstop correction
    hard endstop correction
2019-12-19 started hubel repo
2019-12-19 very rough sketches of machine architecture
2020-01-23 Added 3D files for linear guide test
2020-01-23 added youtube scrrenshot
2020-01-23 Started docu in readme file
2020-01-23 fixed type
2020-02-24 Renamed bootstrap machine to hootstrap
2020-02-28 Pics from skelleftea
2020-04-11 added new sketch for hubel machine family
2020-04-11 added description and illustrations
2020-04-11 fixed typos
2020-04-12 Minor spelling error in title
2020-04-14 fixed print orientation for easy printing
2020-04-14 Added missing step file
2020-05-03 Added wood humphrey pics
2020-05-03 added lots of pictures and text
2020-05-04 added photo descriptions
2020-05-04 Tweked order, fixed index and updated tuning guide
2020-05-04 tweaked index
2020-05-05 Fixed a link
2020-05-07 improved rack and pinion files
2020-05-07 added freecad rack and pinion generator
2020-05-07 temp fix freecad file
2020-05-07 updated freecad rack and pinion generator
2020-05-07 organized rack and pinion files into different folders
2020-05-08 added visuual version of rack and pinion svg
2020-05-08 added-eccentric-bearing-bushing
2020-05-08 added more ilustrations of eccentric bushing
2020-05-09 added illustration of gears
2020-05-09 adde-new-rack-and-pinion-screenshot
2020-05-12 Added link to hector repo
2020-05-12 moved outdated projects to archive
    archive link: https://github.com/fellesverkstedet/fabricatable-machines-archive
2020-05-12 moved theory folder to wiki-media folder
2020-05-12 moved hertz to module development
2020-05-18 updated freecad generator
    now with dust relief and sophistated pinion between teeth skin
2020-05-19 fiex bug casuin spikes in pinion
    a placment rotation axis for a loft slicer was -1 not 1
2020-05-30 added troubleshooting illustration
2020-05-30 Added troubleshooting and diy track roller alternative
2020-06-01 started work on proper axis
2020-06-01 added images of peope raxis sketch
2020-06-01 aded belt gearbox files
2020-06-01 added images of belt gearbox
2020-06-01 added illustraion of modules - axes - machines
2020-06-04 tweaked schematic
2020-06-04 started work on herring axis
2020-06-12 retaking highway after the corona-holidays
2020-06-13 it was hobo not humpfrey
2020-06-13 uart first attempt no luck
2020-06-13 fix swapped X and Y motors
2020-06-13 inductive proximity sensors
2020-06-13 resize images
2020-06-14 spindle sensor
2020-06-15 manual in counter information
2020-06-20 added linear and rotary herring axis generators
2020-06-20 added stl files for 3D print
2020-06-22 added images of herring axis tests
2020-06-22 added docu of alu herring axis
2020-06-23 Added c-beam profile to sketch
2020-06-23 added hold down and Y axis ideas
2020-07-08 Started documentation on fab_factory
2020-07-08 fixed image link?
2020-07-08 Update doc
2020-07-08 updated drawings
2020-07-08 fixed image link
2020-07-18 started work on a feecad model of extrusion auger
    got stuck with a boolean operation of a lofted and a swept solid
2020-11-17 A new voyage begins
2020-11-19 Added GT2 pulleys and link to generator
2020-11-19 cad files for 3d printed axle
2020-11-19 progress in assembly
2020-11-20 new axle iteration
2020-11-20 improved axis assembly
2020-11-20 design progress
2020-11-22 new progress
2020-11-23 started work on tension carriages. also updated axle design to 64teeth
2020-11-27 L based single carrige hack test
2020-11-30 started work on new axis type
2020-12-05 more h beam dev
2020-12-05 added c beam based 3D sketch and illustriations
2020-12-05 added c beam based sketches
2021-02-22 added TEI2020 paper
2021-02-26 old files, but needed push
2021-02-26 first push on new generator in Grasshopper
2021-03-13 housekeeping, moving files
2021-03-13 restructered landing page
2021-03-13 more tweaking
2021-03-13 more landing page tweaking
2021-03-13 Added extra image
2021-03-13 Added machine family
2021-03-15 added recitation links
2021-03-15 added images of humphrey11 in the making
2021-03-16 added axis plane and a new orient axis plane component. also added hulti example
2021-03-16 removed redundant grouping of sliders from testing
2021-04-12 made test clusters for mounting holes for bracket
2021-06-07 connections_hrbl_shield_inkscape
2021-06-07 Updated line colors and width
2021-06-07 Added connections diagram
2021-08-04 started hanzo repo
2021-08-13 fixed symmetry error in vertical Y walls
2021-09-07 removed freecad backups
2021-09-07 added readme and started work on assembly file
2021-09-07 cad progress
2021-09-09 more cad dev
2021-09-12 more dev
2021-10-02 Started hattorini research page
2021-10-03 added simpler option
2021-10-08 added hattorini sketch
2021-10-15 gantry design progress
2021-10-18 Started docu page for Henning CNC
2021-10-18 updated BOM
2021-10-25 log update and more cad dev
2021-11-14 added pics for wiki
2021-12-07 finished bed design
2022-02-14 work on z towers
2022-02-15 progress on z tower - added pinions
2022-02-16 house keeping
2022-02-16 design progress on x carriage
2022-02-17 design progress on z tower and pinions
2022-02-18 z carriage done
2022-02-18 work on x carriage
2022-02-18 more x carriage progress and docu
2022-02-19 z tower, z carriage and x carriage done
2022-02-19 tweaked hole positions and updated step exports
2022-02-20 added rack
2022-02-23 small parts
2022-03-03 added some docu and accessory parts
2022-03-14 docu and dust hose work
2022-03-18 wire management work
2022-03-19 refined hose clamps + house keeping
2022-03-20 added more logo variants
2022-03-20 Migrated the hanzo project
2022-03-28 fixed background for graphic
2023-01-05 added longer version of rack with manual copy paste
2023-02-09 Fixed link to VFD from 1 phase to 3phase out
2023-03-27 added second paper
2025-03-24 added two net charts

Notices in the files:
hrbl-shield/hrbl-grbl_shield_for_jmc_motors/grbl_shield_for_jmc_motors.sch:
License: Creative commons CC BY-SA 4.0
